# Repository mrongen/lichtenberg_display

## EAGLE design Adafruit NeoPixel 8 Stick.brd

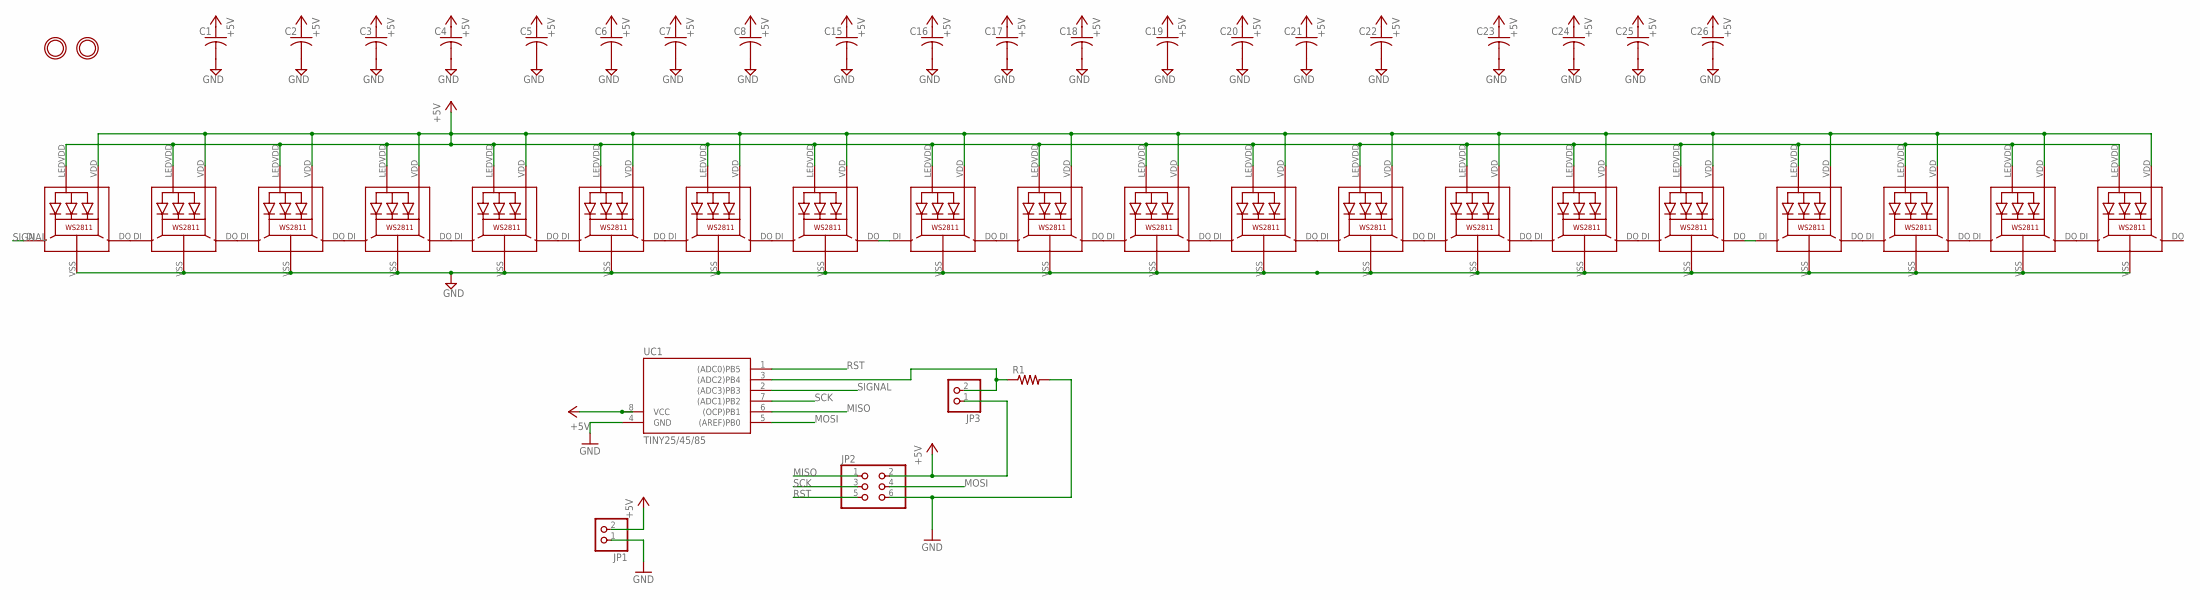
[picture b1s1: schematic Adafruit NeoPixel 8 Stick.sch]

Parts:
C1, C2, C3, C4, C5, C6, C7, C8, C15, C16, C17, C18, C19, C20, C21, C22, C23, C24, C25, C26: C-USC0805K; C0805K
JP1, JP3: PINHD-1X02_2.54; 1X02
JP2: PINHD-2X03_2.54; 2X03
LED1, LED2, LED3, LED4, LED5, LED6, LED7, LED8, LED11, LED12, LED13, LED14, LED15, LED16, LED17, LED18, LED19, LED20, LED21, LED22: WS28115050
R1: R-US_M0805; M0805
U$2, U$3: MOUNTINGHOLE2.0; MOUNTINGHOLE_2.0_PLATED
UC1: TINY25/45/85; SOIC8

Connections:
+5V: C1.1, C2.1, C3.1, C4.1, C5.1, C6.1, C7.1, C8.1, C15.1, C16.1, C17.1, C18.1, C19.1, C20.1, C21.1, C22.1, C23.1, C24.1, C25.1, C26.1, JP1.2, JP2.2, JP3.1, LED1.LEDVDD, LED1.VDD, LED2.LEDVDD, LED2.VDD, LED3.LEDVDD, LED3.VDD, LED4.LEDVDD, LED4.VDD, LED5.LEDVDD, LED5.VDD, LED6.LEDVDD, LED6.VDD, LED7.LEDVDD, LED7.VDD, LED8.LEDVDD, LED8.VDD, LED11.LEDVDD, LED11.VDD, LED12.LEDVDD, LED12.VDD, LED13.LEDVDD, LED13.VDD, LED14.LEDVDD, LED14.VDD, LED15.LEDVDD, LED15.VDD, LED16.LEDVDD, LED16.VDD, LED17.LEDVDD, LED17.VDD, LED18.LEDVDD, LED18.VDD, LED19.LEDVDD, LED19.VDD, LED20.LEDVDD, LED20.VDD, LED21.LEDVDD, LED21.VDD, LED22.LEDVDD, LED22.VDD, UC1.8 (VCC)
GND: C1.2, C2.2, C3.2, C4.2, C5.2, C6.2, C7.2, C8.2, C15.2, C16.2, C17.2, C18.2, C19.2, C20.2, C21.2, C22.2, C23.2, C24.2, C25.2, C26.2, JP1.1, JP2.6, LED1.VSS (GND), LED2.VSS (GND), LED3.VSS (GND), LED4.VSS (GND), LED5.VSS (GND), LED6.VSS (GND), LED7.VSS (GND), LED8.VSS (GND), LED11.VSS (GND), LED12.VSS (GND), LED13.VSS (GND), LED14.VSS (GND), LED15.VSS (GND), LED16.VSS (GND), LED17.VSS (GND), LED18.VSS (GND), LED19.VSS (GND), LED20.VSS (GND), LED21.VSS (GND), LED22.VSS (GND), R1.2, UC1.4 (GND)
MISO: JP2.1, UC1.6 ((OCP)PB1)
MOSI: JP2.4, UC1.5 ((AREF)PB0)
unnamed: LED1.DO, LED2.DI
unnamed: LED2.DO, LED3.DI
unnamed: LED3.DO, LED4.DI
unnamed: LED4.DO, LED5.DI
unnamed: LED5.DO, LED6.DI
unnamed: LED6.DO, LED7.DI
unnamed: LED7.DO, LED8.DI
unnamed: LED11.DO, LED12.DI
unnamed: JP3.2, R1.1, UC1.3 ((ADC2)PB4)
unnamed: LED12.DO, LED13.DI
unnamed: LED13.DO, LED14.DI
unnamed: LED14.DO, LED15.DI
unnamed: LED15.DO, LED16.DI
unnamed: LED16.DO, LED17.DI
unnamed: LED17.DO, LED18.DI
unnamed: LED19.DO, LED20.DI
unnamed: LED20.DO, LED21.DI
unnamed: LED21.DO, LED22.DI
unnamed: LED8.DO, LED11.DI
unnamed: LED18.DO, LED19.DI
RST: JP2.5, UC1.1 ((ADC0)PB5)
SCK: JP2.3, UC1.7 ((ADC1)PB2)
SIGNAL: LED1.DI, UC1.2 ((ADC3)PB3)

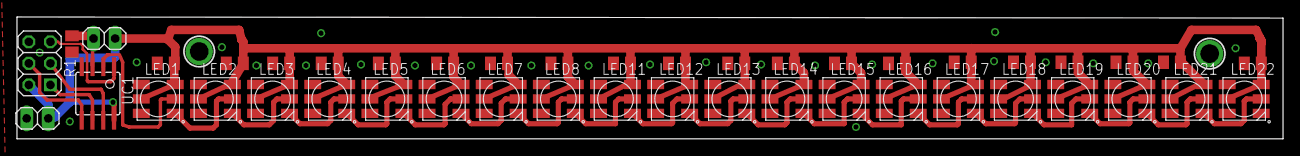
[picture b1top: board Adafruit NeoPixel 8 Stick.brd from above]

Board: 2 copper layers, 149.1 x 14.4 mm, 48 parts (1 on the bottom side), 27 nets.

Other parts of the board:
U$1: ADAFRUIT_TEXT_20MM

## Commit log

2014-04-26 first commit
    schematic, and board

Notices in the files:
parts and their libraries:
microbuilder: This work is placed in the public domain, and may be freely used for commercial and non-commercial work with the following conditions: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
